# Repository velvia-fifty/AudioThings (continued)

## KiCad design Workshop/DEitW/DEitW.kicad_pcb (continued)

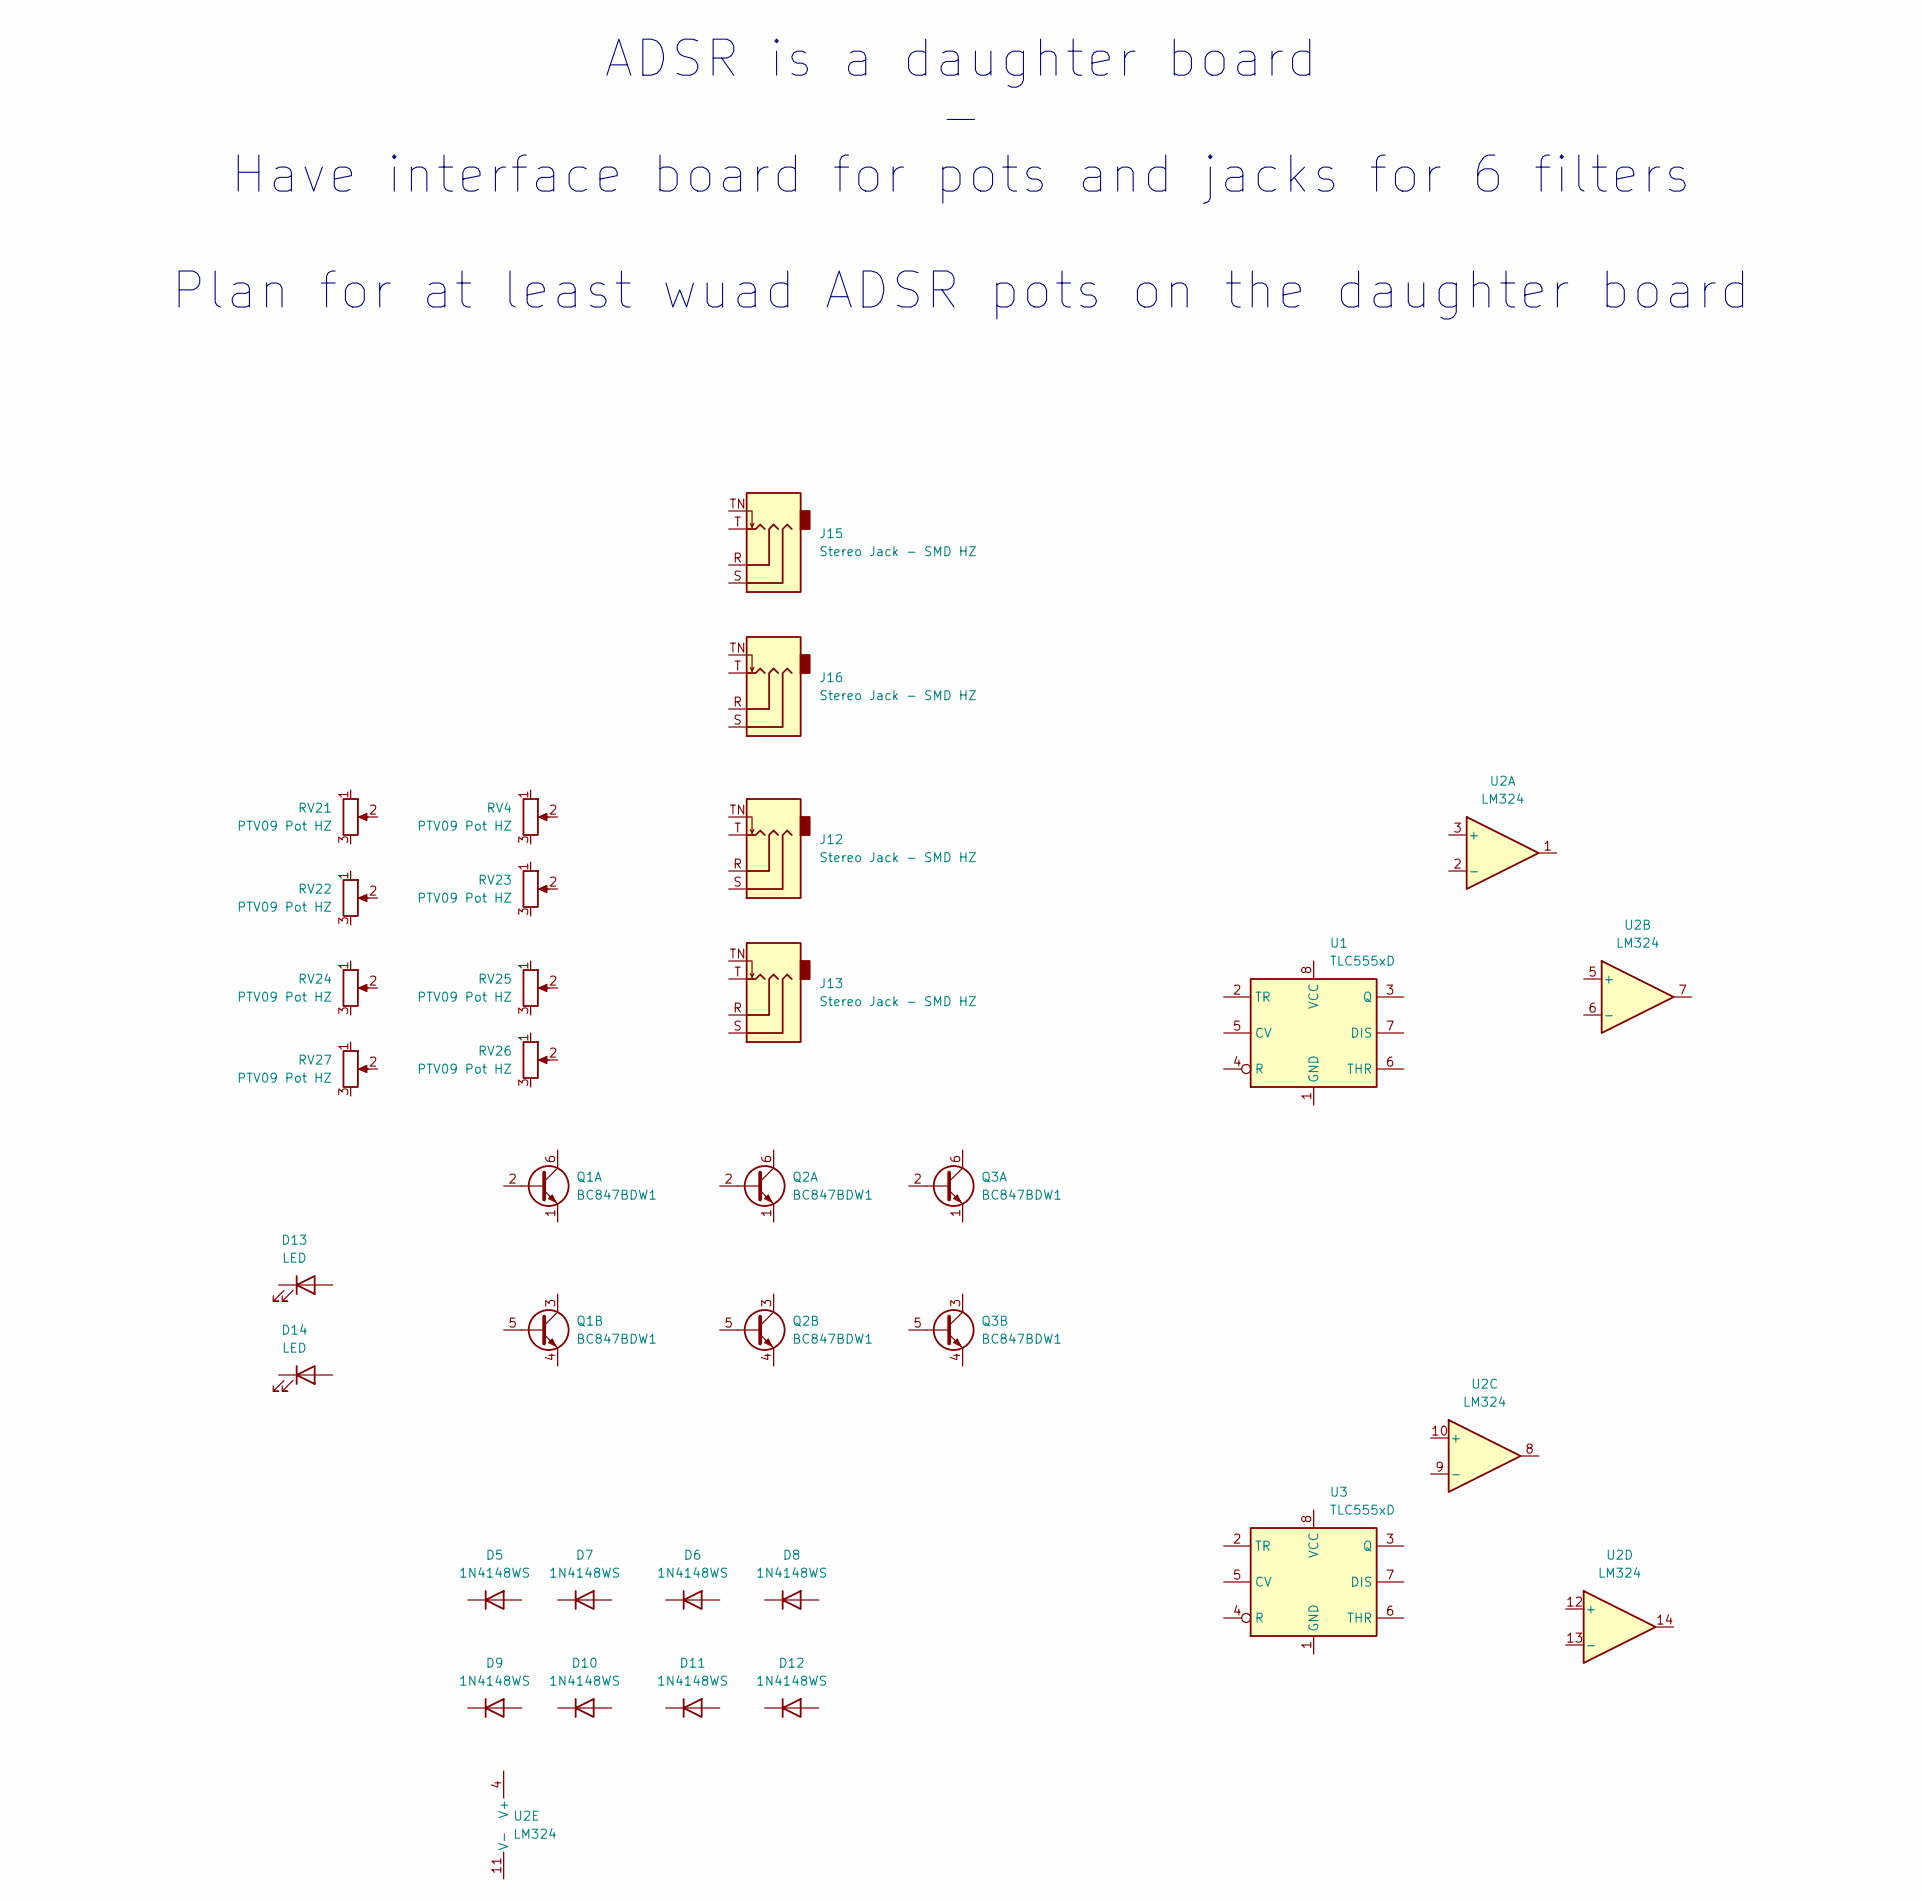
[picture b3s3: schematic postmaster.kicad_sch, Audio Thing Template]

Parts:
D5, D6, D7, D8, D9, D10, D11, D12: 1N4148WS; D_SOD-323
D13, D14: LED; LED_0805_2012Metric
J12, J13, J15, J16: Stereo Jack - SMD HZ; SMD_STEREO_CUI_SJ-3524-SMT_Horizontal
Q1, Q2, Q3: BC847BDW1; SOT-363_SC-70-6
RV4, RV21, RV22, RV23, RV24, RV25, RV26, RV27: PTV09 Pot HZ; Twelve_Turn_Trim_Bourns_3224J_Horizontal
U1, U3: TLC555xD; SOIC-8_3.9x4.9mm_P1.27mm
U2: LM324

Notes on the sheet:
ADSR is a daughter board - Have interface board for pots and jacks for 6 filters Plan for at least wuad ADSR pots on the daughter board

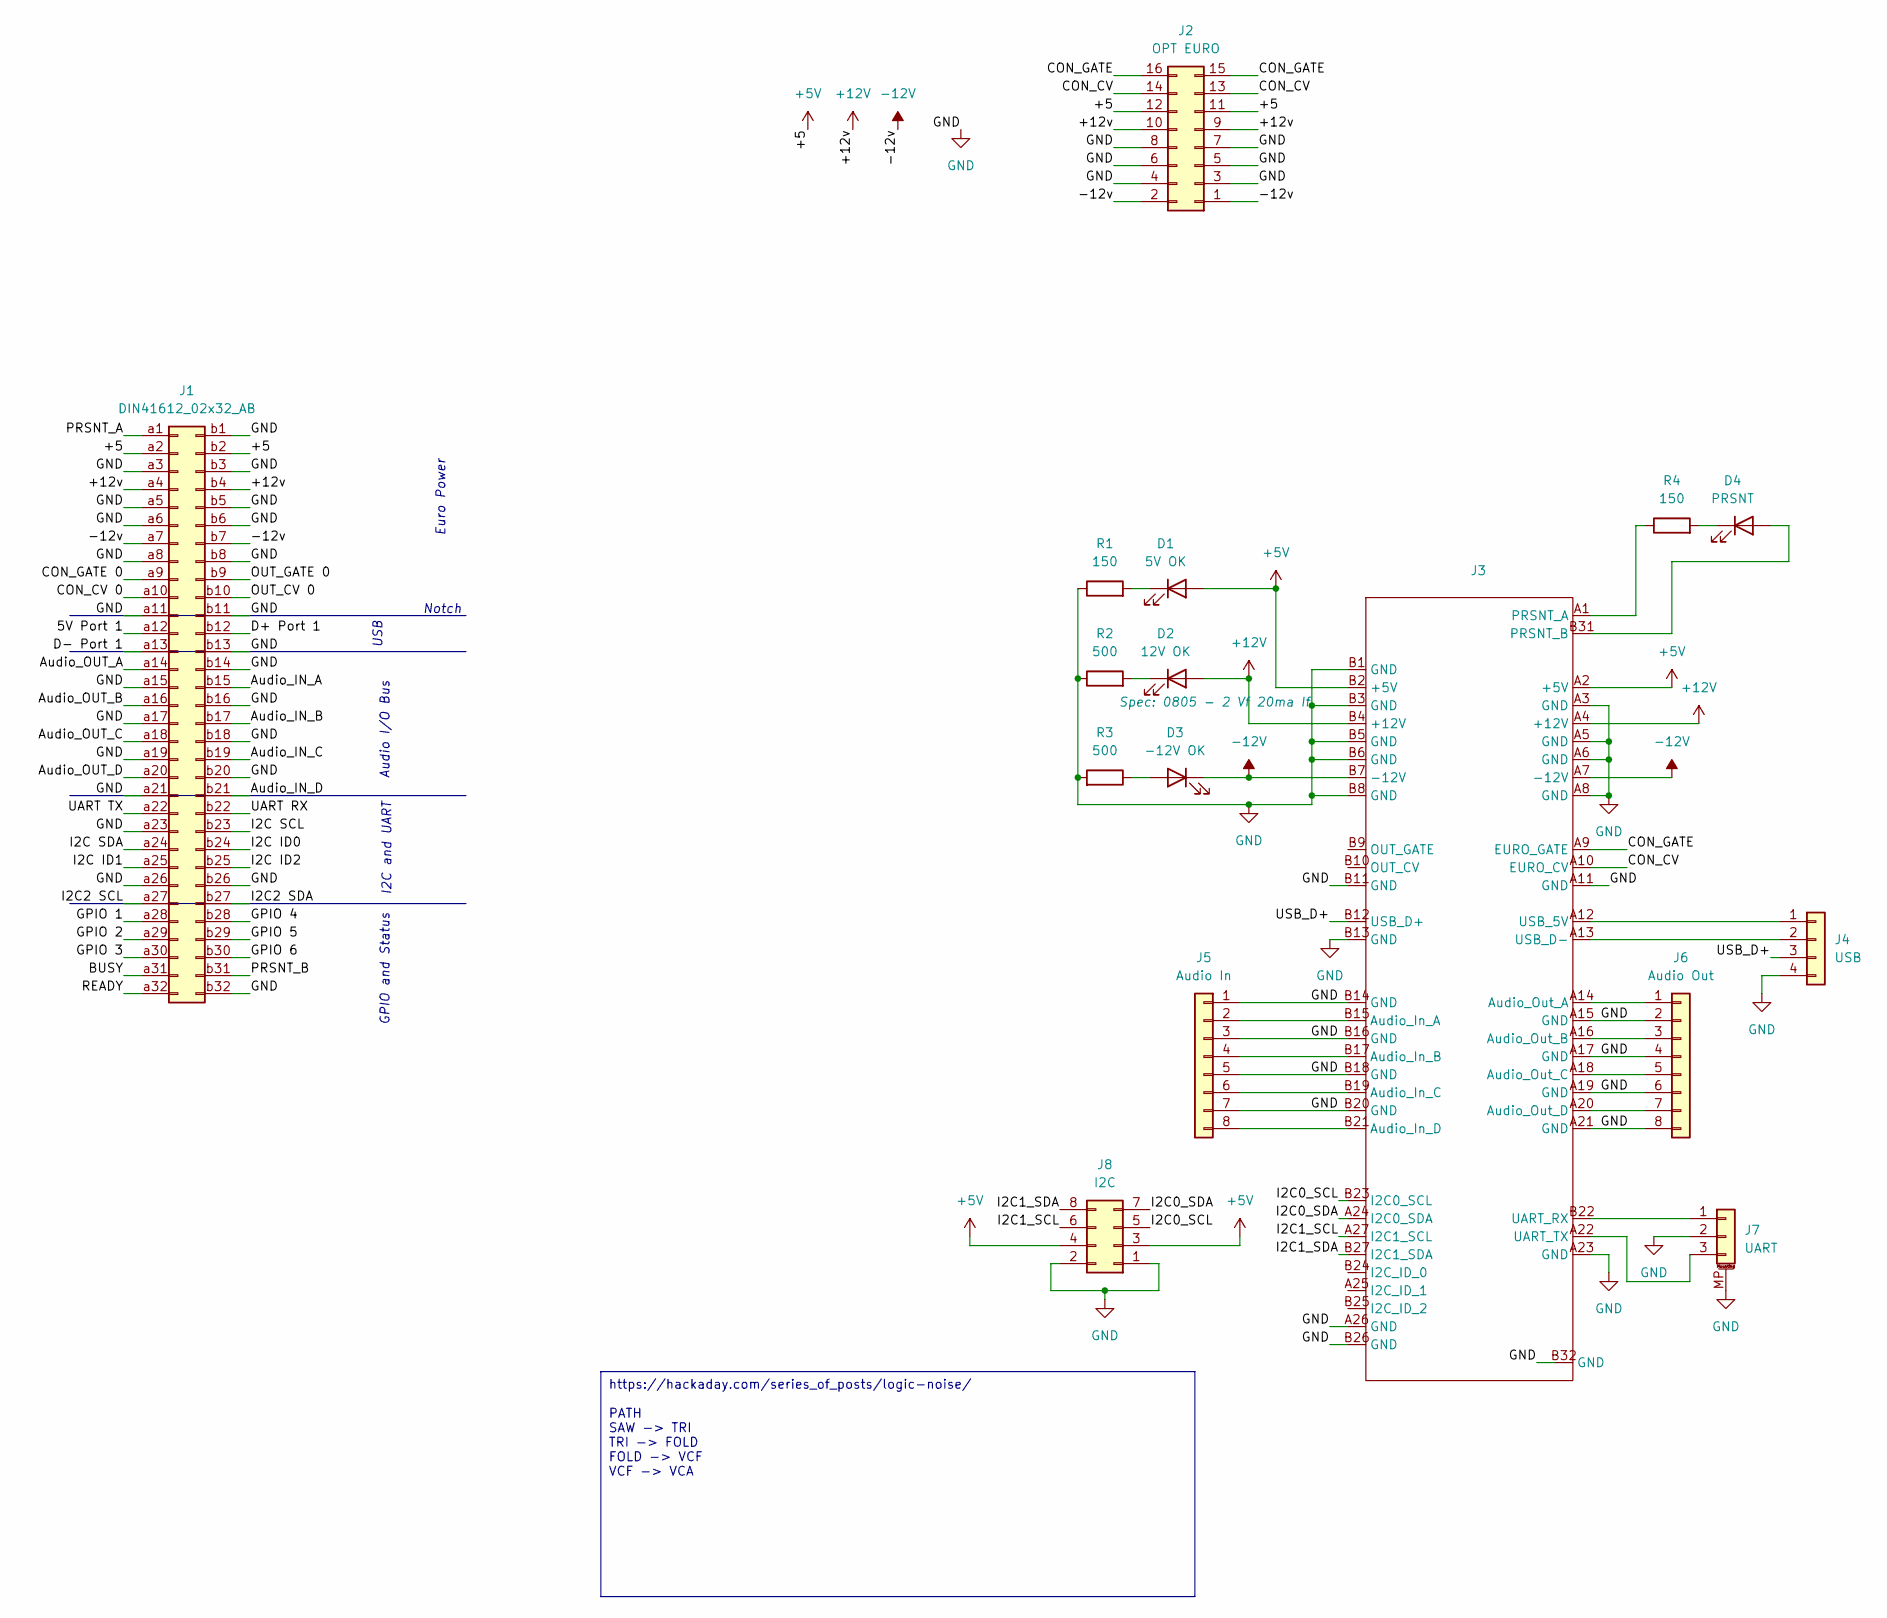
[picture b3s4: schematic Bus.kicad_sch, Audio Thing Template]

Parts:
D1: 5V OK; LED_0805_2012Metric_Pad1.15x1.40mm_HandSolder
D2: 12V OK; LED_0805_2012Metric_Pad1.15x1.40mm_HandSolder
D3: -12V OK; LED_0805_2012Metric_Pad1.15x1.40mm_HandSolder
D4: PRSNT; LED_0805_2012Metric_Pad1.15x1.40mm_HandSolder
J1: DIN41612_02x32_AB
J2: OPT EURO; EURORACK Right Angle
J3: BUS_PCIexpress_x4
J4: USB; PinHeader_1x04_P2.54mm_Vertical; Part Number 1-0401FBV0T
J5: Audio In; AMPHENOL_F33B-1A7Q1-E8C08
J6: Audio Out; AMPHENOL_F33B-1A7Q1-E8C08
J7: UART; CONN_BM03B-SRSS-TBLFSN_JST
J8: I2C; PinHeader_2x04_P2.54mm_Vertical
R1, R4: 150; R_0805_2012Metric_Pad1.20x1.40mm_HandSolder
R2, R3: 500; R_0805_2012Metric_Pad1.20x1.40mm_HandSolder

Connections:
+5V: D1.2 (A), J1.a2, J1.b2, J2.11, J2.12, J3.A2 (+5V), J3.B2 (+5V), J8.3, J8.4
+12V: D2.2 (A), J1.a4, J1.b4, J2.9, J2.10, J3.A4 (+12V), J3.B4 (+12V)
-12V: D3.1 (K), J1.a7, J1.b7, J2.1, J2.2, J3.A7 (-12V), J3.B7 (-12V)
/Bus/CON_CV: J2.13, J2.14, J3.A10 (EURO_CV)
/Bus/CON_GATE: J2.15, J2.16, J3.A9 (EURO_GATE)
/Bus/I2C0_SCL: J3.B23 (I2C0_SCL), J8.5
/Bus/I2C0_SDA: J3.A24 (I2C0_SDA), J8.7
/Bus/I2C1_SCL: J3.A27 (I2C1_SCL), J8.6
/Bus/I2C1_SDA: J3.B27 (I2C1_SDA), J8.8
/Bus/USB_D+: J3.B12 (USB_D+), J4.3
GND: J1.a3, J1.a5, J1.a6, J1.a8, J1.a11, J1.a15, J1.a17, J1.a19, J1.a21, J1.a23, J1.a26, J1.b1, J1.b3, J1.b5, J1.b6, J1.b8, J1.b11, J1.b13, J1.b14, J1.b16, J1.b18, J1.b20, J1.b26, J1.b32, J2.3, J2.4, J2.5, J2.6, J2.7, J2.8, J3.A3 (GND), J3.A5 (GND), J3.A6 (GND), J3.A8 (GND), J3.A11 (GND), J3.A15 (GND), J3.A17 (GND), J3.A19 (GND), J3.A21 (GND), J3.A23 (GND), J3.A26 (GND), J3.B1 (GND), J3.B3 (GND), J3.B5 (GND), J3.B6 (GND), J3.B8 (GND), J3.B11 (GND), J3.B13 (GND), J3.B14 (GND), J3.B16 (GND), J3.B18 (GND), J3.B20 (GND), J3.B26 (GND), J3.B32 (GND), J4.4, J5.1, J5.3, J5.5, J5.7, J6.2, J6.4, J6.6, J6.8, J7.2, J7.MP (MountPin), J8.1, J8.2, R1.1, R2.1, R3.2; also elsewhere on the board
unnamed: D1.1 (K), R1.2
unnamed: D2.1 (K), R2.2
unnamed: D3.2 (A), R3.1
unnamed: D4.2 (A), J3.B31 (PRSNT_B)
unnamed: D4.1 (K), R4.2
unnamed: J3.B15 (Audio_In_A), J5.2
unnamed: J3.B17 (Audio_In_B), J5.4
unnamed: J3.B19 (Audio_In_C), J5.6
unnamed: J3.B21 (Audio_In_D), J5.8
unnamed: J3.A14 (Audio_Out_A), J6.1
unnamed: J3.A16 (Audio_Out_B), J6.3
unnamed: J3.A18 (Audio_Out_C), J6.5
unnamed: J3.A20 (Audio_Out_D), J6.7
unnamed: J3.A1 (PRSNT_A), R4.1
unnamed: J3.B22 (UART_RX), J7.1
unnamed: J3.A22 (UART_TX), J7.3
unnamed: J3.A12 (USB_5V), J4.1
unnamed: J3.A13 (USB_D-), J4.2

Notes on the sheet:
https://hackaday.com/series_of_posts/logic-noise/ PATH SAW -> TRI TRI -> FOLD FOLD -> VCF VCF -> VCA
Audio I/O Bus
USB
Notch
Euro Power
GPIO and Status
I2C and UART

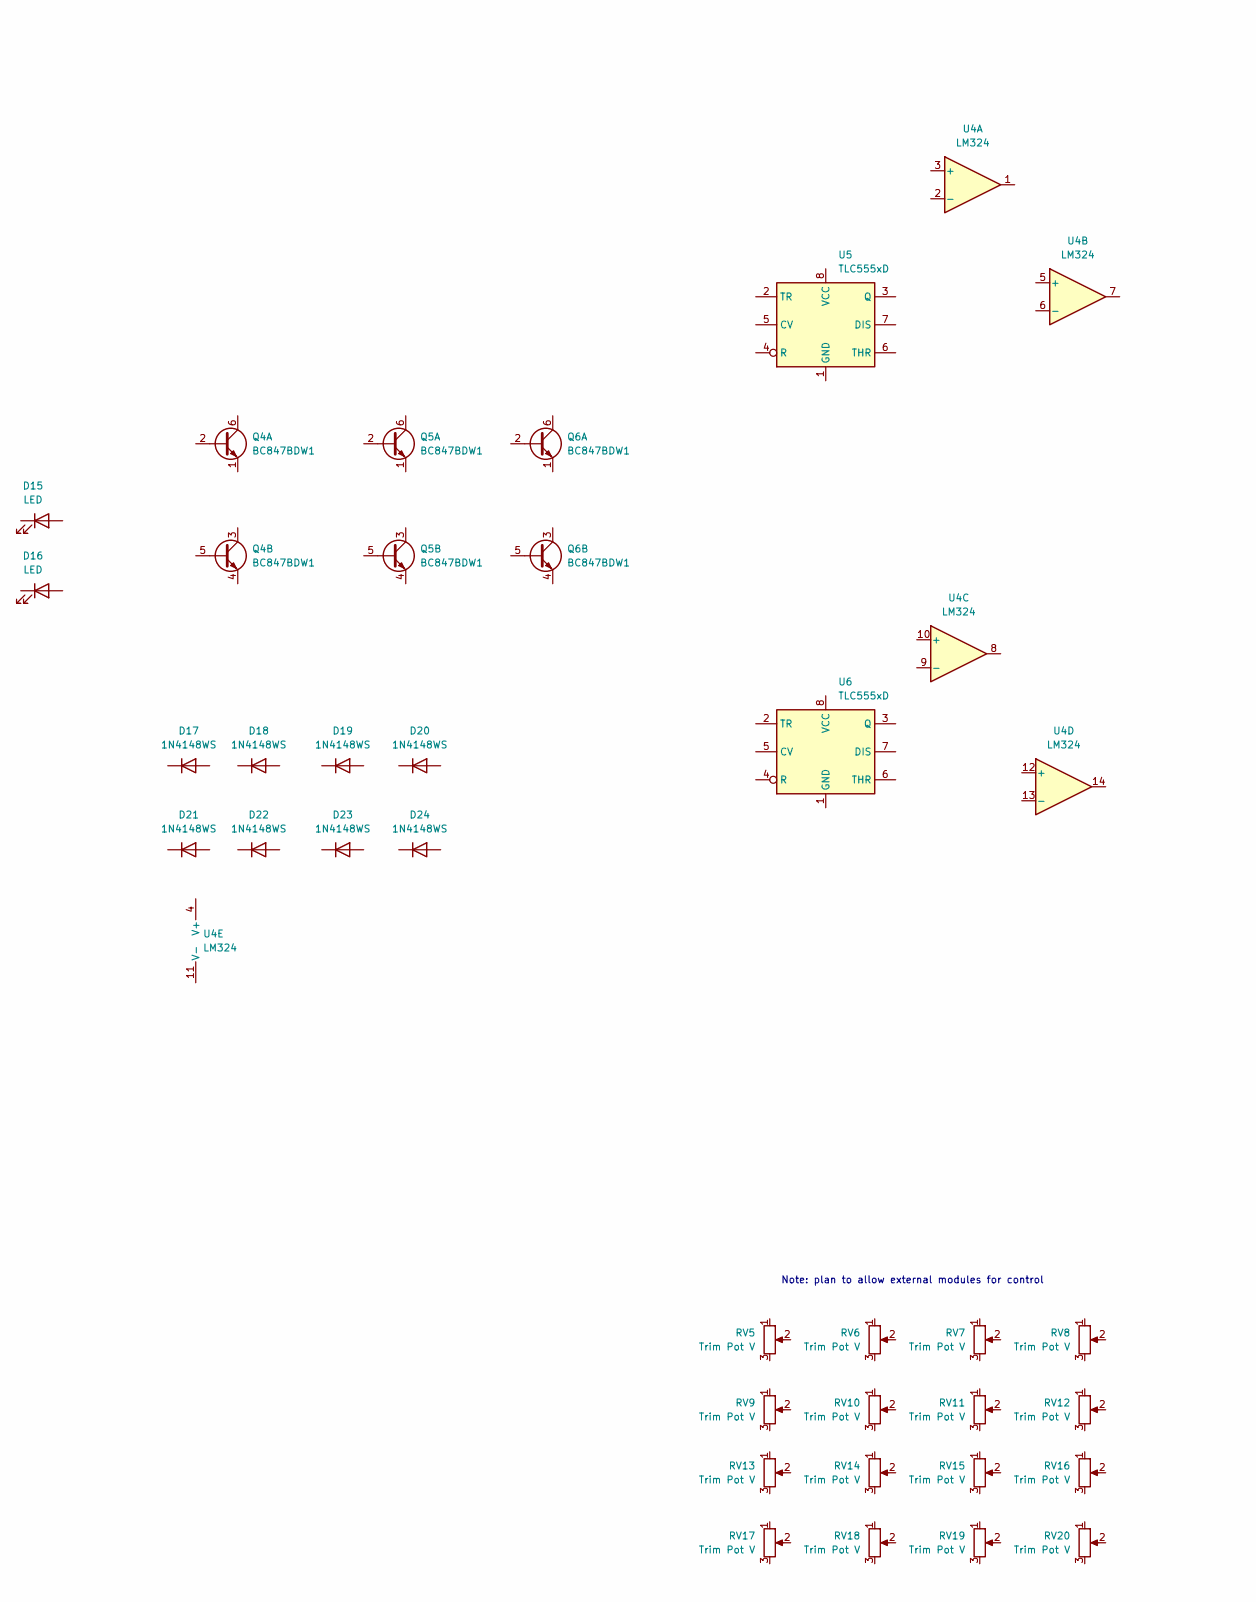
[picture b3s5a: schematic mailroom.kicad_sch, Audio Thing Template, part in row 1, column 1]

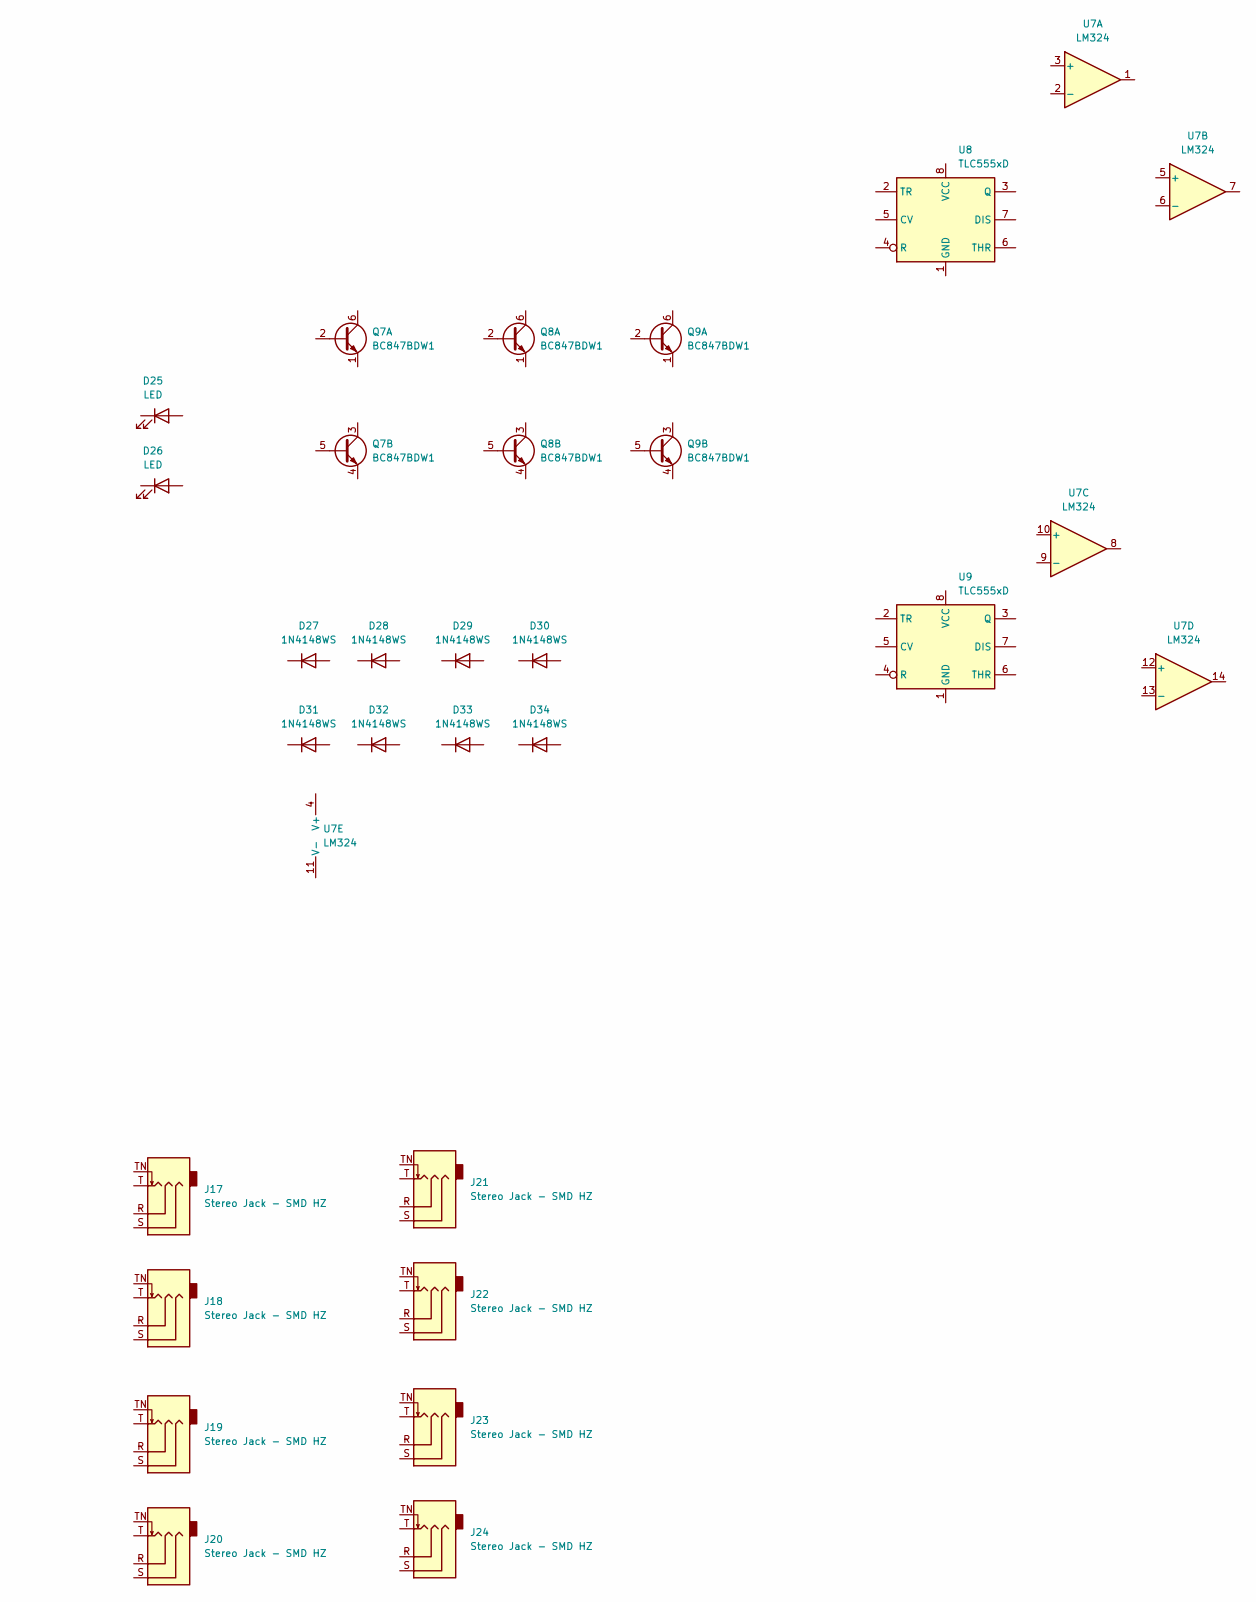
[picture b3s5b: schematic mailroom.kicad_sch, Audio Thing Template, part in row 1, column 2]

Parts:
D15, D16, D25, D26: LED; LED_0805_2012Metric
D17, D18, D19, D20, D21, D22, D23, D24, D27, D28, D29, D30, D31, D32, D33, D34: 1N4148WS; D_SOD-323
J17, J18, J19, J20, J21, J22, J23, J24: Stereo Jack - SMD HZ; SMD_STEREO_CUI_SJ-3524-SMT_Horizontal
Q4, Q5, Q6, Q7, Q8, Q9: BC847BDW1; SOT-363_SC-70-6
RV5, RV6, RV7, RV8, RV9, RV10, RV11, RV12, RV13, RV14, RV15, RV16, RV17, RV18, RV19, RV20: Trim Pot V; Twelve_Turn_Trim_Bourns_3224J_Horizontal
U4, U7: LM324
U5, U6, U8, U9: TLC555xD; SOIC-8_3.9x4.9mm_P1.27mm

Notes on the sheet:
Note: plan to allow external modules for control

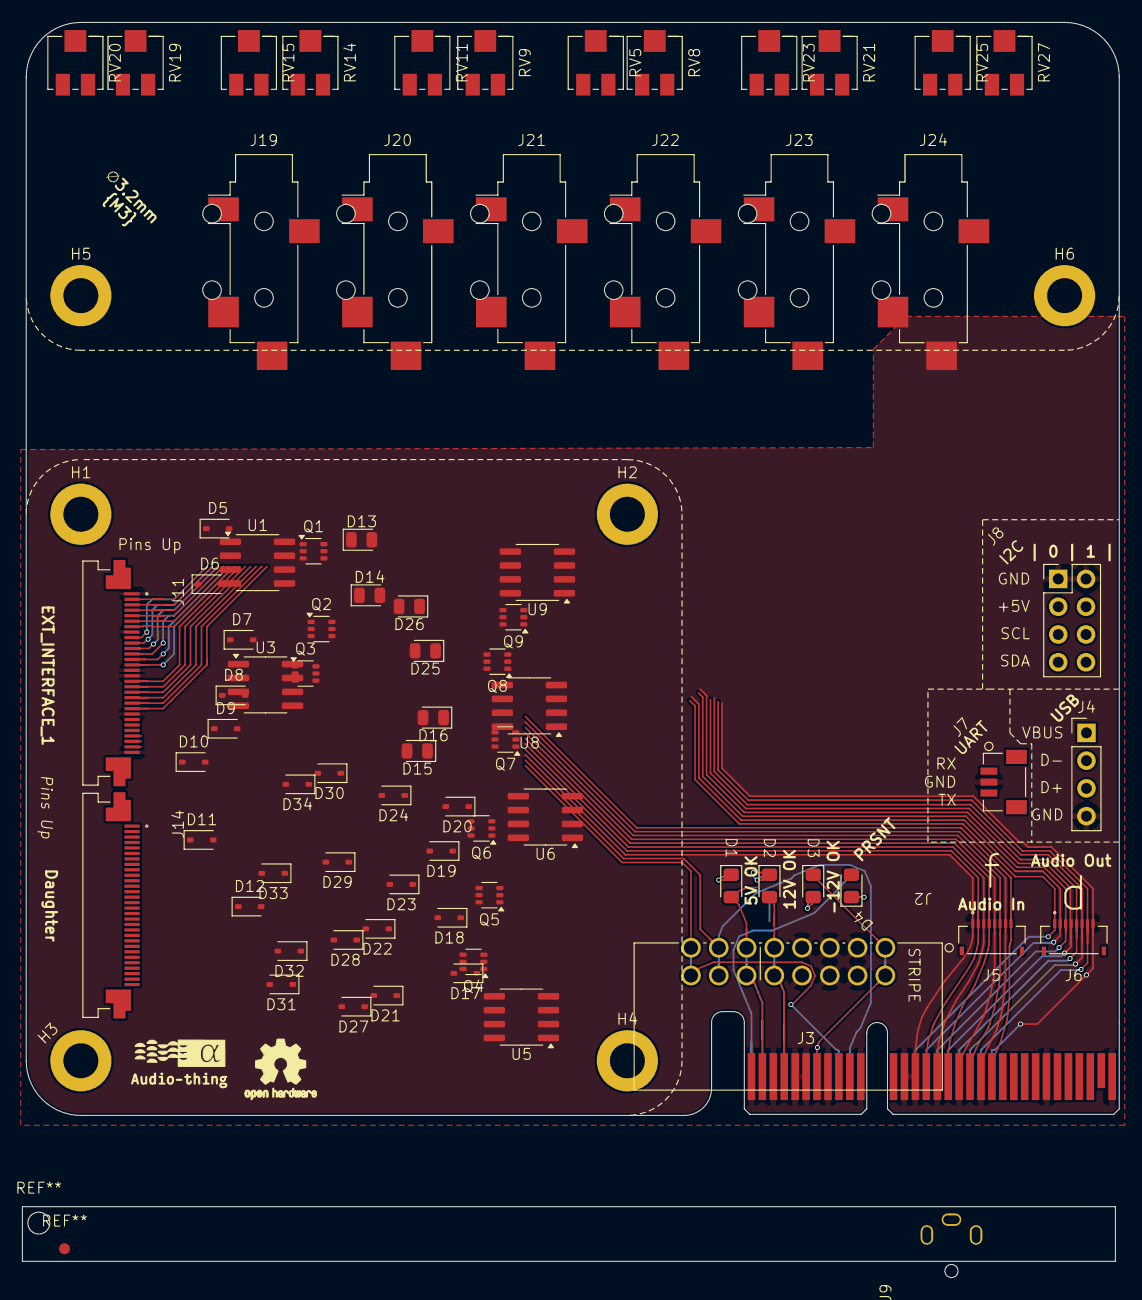
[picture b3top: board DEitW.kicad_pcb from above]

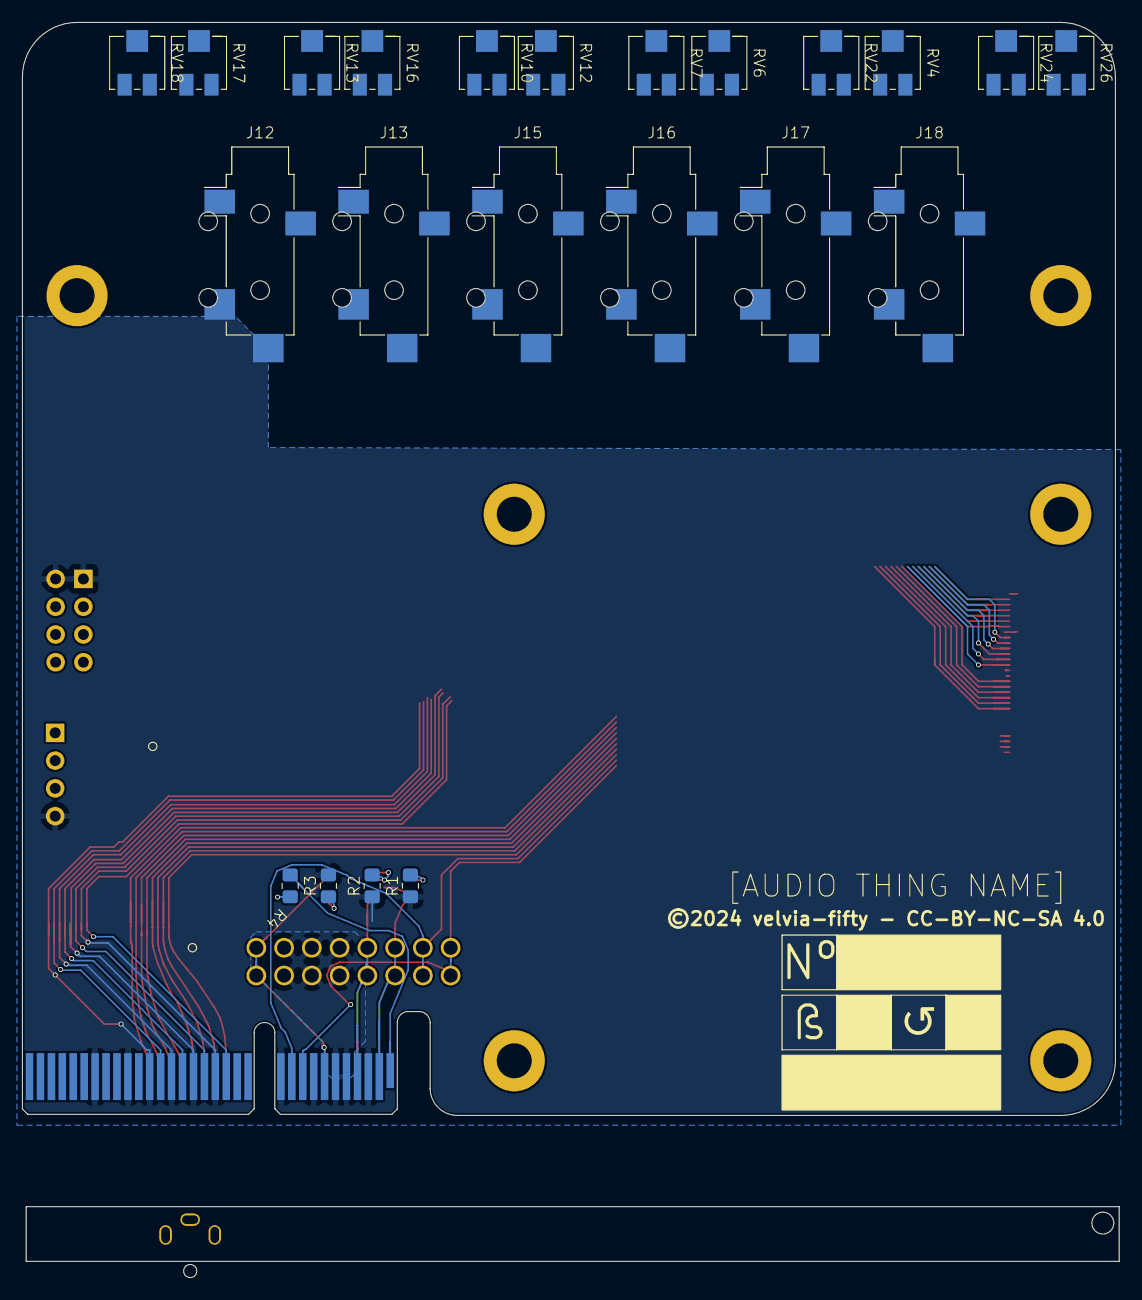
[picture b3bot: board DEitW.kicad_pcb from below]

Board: 2 copper layers, 100.0 x 100.0 mm, 105 parts (22 on the bottom side), 29 nets.

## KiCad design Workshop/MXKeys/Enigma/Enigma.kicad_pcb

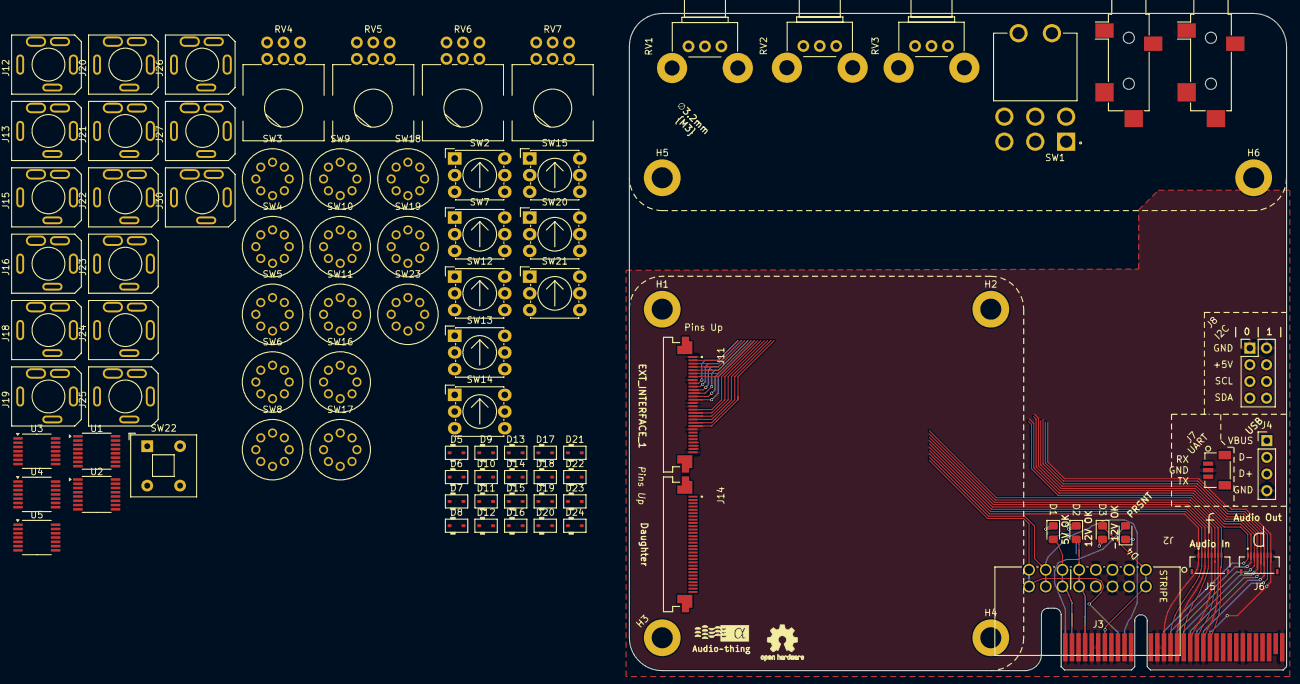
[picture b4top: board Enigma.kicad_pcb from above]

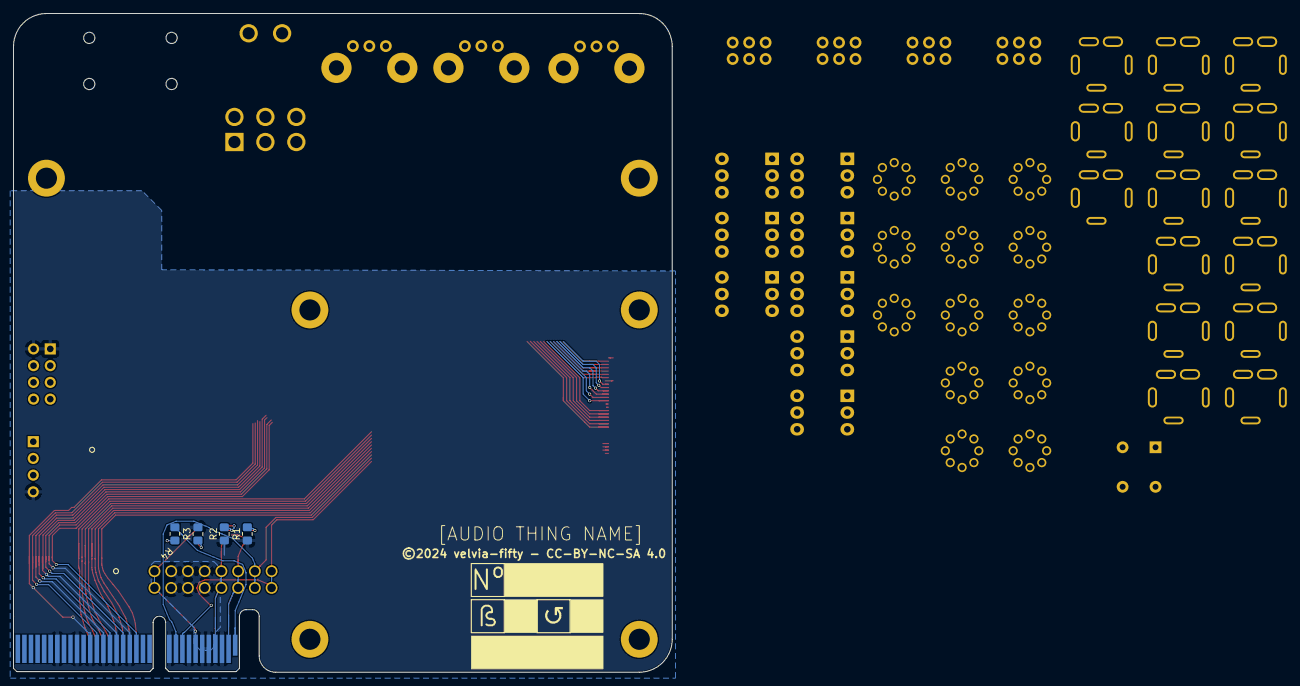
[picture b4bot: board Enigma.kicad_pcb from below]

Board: 2 copper layers, 100.0 x 100.0 mm, 95 parts (4 on the bottom side), 79 nets.

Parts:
D1: 5V OK; LED_0805_2012Metric_Pad1.15x1.40mm_HandSolder
D2: 12V OK; LED_0805_2012Metric_Pad1.15x1.40mm_HandSolder
D3: -12V OK; LED_0805_2012Metric_Pad1.15x1.40mm_HandSolder
D4: PRSNT; LED_0805_2012Metric_Pad1.15x1.40mm_HandSolder
D5, D6, D7, D8, D9, D10, D11, D12, D13, D14, D15, D16, D17, D18, D19, D20, D21, D22, D23, D24: 1N4148WS; D_SOD-323
H1, H2, H3, H4, H5, H6: M3; MountingHole_3.2mm_M3_DIN965_Pad
J2: OPT EURO; EURORACK Right Angle
J3: BUS_PCIexpress_x4
J4: USB; PinHeader_1x04_P2.54mm_Vertical
J5: Audio In; AMPHENOL_F33B-1A7Q1-E8C08
J6: Audio Out; AMPHENOL_F33B-1A7Q1-E8C08
J7: UART; CONN_BM03B-SRSS-TBLFSN_JST
J8: I2C; PinHeader_2x04_P2.54mm_Vertical
J9, J10: Stereo Jack - SMD HZ; SMD_STEREO_CUI_SJ-3524-SMT_Horizontal
J11: EXT_INTERFACE_1; AMPHENOL_SFV30R-4STE1HLF - FFC - 30 RA
J12: Input 1; SJ3-3505
J13: Input 2; SJ3-3505
J14: Daughter; AMPHENOL_SFV30R-4STE1HLF - FFC - 30 RA
J15: Input 3; SJ3-3505
J16: Input 4; SJ3-3505
J18: Filter EXT 2; SJ3-3505
J19: Filter EXT 3; SJ3-3505
J20: Filter EXT 4; SJ3-3505
J21: Output Bypass 1; SJ3-3505
J22: Mix Out Channel 1; SJ3-3505
J23: Mix Out Channel 2; SJ3-3505
J24: Mix Out Channel 3; SJ3-3505
J25: Mix Out Channel 4; SJ3-3505
J26: Bypass Return/Filter Out 1; SJ3-3505
J27: Mix^{2}; SJ3-3505
J30: Bypass Send/Filter In 1; SJ3-3505
R1, R4: 150; R_0805_2012Metric_Pad1.20x1.40mm_HandSolder
R2, R3: 500; R_0805_2012Metric_Pad1.20x1.40mm_HandSolder
RV1, RV2, RV3: PTV09 Pot HZ; Potentiometer_Bourns_PTV09A-2_Single_Horizontal
RV4, RV5, RV6, RV7: 10k B; 2hp_Alps_RK09L_Double_Vertical
SW1: Micro Toggle; DPDT Micro SW_1825138-7
SW2: Input Route 1; Nidec_Copal_SH-7010C
SW3: Input Handoff R 1; RM-SWITCH
SW4: Input Handoff R 2; RM-SWITCH
SW5: Input Handoff L 2; RM-SWITCH
SW6: Input Handoff L 1; RM-SWITCH
SW7: Input Route 2; Nidec_Copal_SH-7010C
SW8: Input Handoff R 3; RM-SWITCH
SW9: Input Handoff R 4; RM-SWITCH
SW10: Input Handoff L 3; RM-SWITCH
SW11: Input Handoff L 4; RM-SWITCH
SW12: Input Route 3; Nidec_Copal_SH-7010C
SW13: Input Route 4; Nidec_Copal_SH-7010C
SW14: FIlter Route 1; Nidec_Copal_SH-7010C
SW15: Output Mix 1; Nidec_Copal_SH-7010C
SW16: Stereo Mix R 1; RM-SWITCH
SW17: Stereo Mix R 2; RM-SWITCH
SW18: Stereo Mix R 3; RM-SWITCH
SW19: Stereo Mix R 4; RM-SWITCH
SW20: FIlter Route Bypass; Nidec_Copal_SH-7010C
SW21: Amplifier Route Bypass; Nidec_Copal_SH-7010C
SW22: Bypass?; SW_Push_2P1T_Toggle_CK_PVA1xxH1xxxxxxV2
SW23: Control Config; RM-SWITCH
U1, U2: DG403DVZ; TSSOP-16_4.4x5mm_P0.65mm
U3: 40106; TSSOP-14_4.4x5mm_P0.65mm
U4, U5: CD4066BPW; TSSOP-14_4.4x5mm_P0.65mm

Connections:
5v: SW22.1, SW22.3, U1.12 (VL), U2.12 (VL)
+5V: D1.2 (A), J2.11, J2.12, J3.A2 (+5V), J3.B2 (+5V), J8.3, J8.4
+12v: D2.2 (A), J2.9, J2.10, J3.A4 (+12V), J3.B4 (+12V), U1.11 (V+), U2.11 (V+)
-12v: D3.1 (K), J2.1, J2.2, J3.A7 (-12V), J3.B7 (-12V), U1.14 (V-), U2.14 (V-)
/Assert All Inputs: J12.T, J13.T, J15.T, J16.T, SW2.C, SW3.5, SW3.6, SW3.7, SW4.5, SW4.6, SW4.7, SW5.5, SW5.6, SW5.7, SW5.8, SW6.5, SW6.6, SW6.7, SW6.8, SW7.C, SW8.5, SW8.6, SW8.7, SW9.5, SW9.6, SW9.7, SW10.5, SW10.6, SW10.7, SW10.8, SW11.5, SW11.6, SW11.7, SW11.8, SW12.C, SW13.C, SW16.5, SW17.5, SW18.5, SW19.5, U4.1, U4.4, U4.8, U4.11
/Bus/CON_CV: J2.13, J2.14, J3.A10 (EURO_CV)
/Bus/CON_GATE: J2.15, J2.16, J3.A9 (EURO_GATE)
/Bus/I2C0_SCL: J3.B23 (I2C0_SCL), J8.5
/Bus/I2C0_SDA: J3.A24 (I2C0_SDA), J8.7
/Bus/I2C1_SCL: J3.A27 (I2C1_SCL), J8.6
/Bus/I2C1_SDA: J3.B27 (I2C1_SDA), J8.8
/Bus/USB_D+: J3.B12 (USB_D+), J4.3
/IN 1 TN: J12.TN, SW4.3, SW5.3, SW8.4, SW9.2, SW10.4, SW11.2
/IN 2 TN: J13.TN, SW3.2, SW6.2, SW8.3, SW9.4, SW10.3, SW11.4
/IN 3 TN: J15.TN, SW3.4, SW4.2, SW5.2, SW6.4, SW9.3, SW11.3
/IN 4 TN: J16.TN, SW3.3, SW4.4, SW5.4, SW6.3, SW8.2, SW10.2
Amplifier 1: D21.2 (A), SW14.1, SW16.7, SW20.1
Amplifier 2: D22.2 (A), SW14.2, SW17.7, SW20.2
Amplifier 3: D23.2 (A), SW14.4, SW18.7, SW20.4
Amplifier 4: D24.2 (A), SW14.8, SW19.7, SW20.8
COM: U1.13 (GND), U2.13 (GND)
Channel 1: J22.T, RV4.3, SW15.1, SW16.2, SW17.4, SW19.3, SW21.1
Channel 2: J23.T, RV5.3, SW15.2, SW16.3, SW17.2, SW18.4, SW21.2
Channel 3: J24.T, RV6.3, SW15.4, SW17.3, SW18.2, SW19.4, SW21.4
Channel 4: J25.T, RV7.3, SW15.8, SW16.4, SW18.3, SW19.2, SW21.8
Filter 1: D5.2 (A), D9.2 (A), D13.2 (A), D17.2 (A), SW2.1, SW7.1, SW12.1, SW13.1, SW16.6, U1.4 (S3), U1.5 (S4), U1.16 (S1)
Filter 2: D6.2 (A), D10.2 (A), D14.2 (A), D18.2 (A), J18.TN, SW2.2, SW7.2, SW12.2, SW13.2, SW17.6
Filter 3: D7.2 (A), D11.2 (A), D15.2 (A), D19.2 (A), J19.TN, SW2.4, SW7.4, SW12.4, SW13.4, SW18.6
Filter 4: D8.2 (A), D12.2 (A), D16.2 (A), D20.2 (A), J20.TN, SW2.8, SW7.8, SW12.8, SW13.8, SW19.6
GND: J2.3, J2.4, J2.5, J2.6, J2.7, J2.8, J3.A3 (GND), J3.A5 (GND), J3.A6 (GND), J3.A8 (GND), J3.A11 (GND), J3.A15 (GND), J3.A17 (GND), J3.A19 (GND), J3.A21 (GND), J3.A23 (GND), J3.A26 (GND), J3.B1 (GND), J3.B3 (GND), J3.B5 (GND), J3.B6 (GND), J3.B8 (GND), J3.B11 (GND), J3.B13 (GND), J3.B14 (GND), J3.B16 (GND), J3.B18 (GND), J3.B20 (GND), J3.B26 (GND), J3.B32 (GND), J4.4, J5.1, J5.3, J5.5, J5.7, J6.2, J6.4, J6.6, J6.8, J7.2, J8.1, J8.2, J11.1, J11.8, J11.15, J11.16, J11.23, J11.30, J12.S, J13.S, J15.S, J16.S, J18.S, J19.S, J20.S, J21.S, J22.S, J23.S, J24.S, J25.S, J26.S, J27.S, J30.S, R1.1, R2.1, R3.2, RV4.1, RV4.4, RV5.1, RV5.4, RV6.1, RV6.4, RV7.1, RV7.4
LPF OUTPUT: U2.5 (S4), U2.16 (S1)
unnamed: D1.1 (K), R1.2
unnamed: D2.1 (K), R2.2
unnamed: D3.2 (A), R3.1
unnamed: D4.2 (A), J3.B31 (PRSNT_B)
unnamed: D4.1 (K), R4.2
unnamed: D5.1 (K), D6.1 (K), D7.1 (K), D8.1 (K), U3.1
unnamed: D9.1 (K), D10.1 (K), D11.1 (K), D12.1 (K), U3.3
unnamed: D13.1 (K), D14.1 (K), D15.1 (K), D16.1 (K), U3.5
unnamed: D17.1 (K), D18.1 (K), D19.1 (K), D20.1 (K), U3.9
unnamed: D21.1 (K), D22.1 (K), D23.1 (K), D24.1 (K), U3.11
unnamed: J3.B15 (Audio_In_A), J5.2
unnamed: J3.B17 (Audio_In_B), J5.4
unnamed: J3.B19 (Audio_In_C), J5.6
unnamed: J3.B21 (Audio_In_D), J5.8
unnamed: J3.A14 (Audio_Out_A), J6.1
unnamed: J3.A16 (Audio_Out_B), J6.3
unnamed: J3.A18 (Audio_Out_C), J6.5
unnamed: J3.A20 (Audio_Out_D), J6.7
unnamed: J3.A1 (PRSNT_A), R4.1
unnamed: J3.B22 (UART_RX), J7.1
unnamed: J3.A22 (UART_TX), J7.3
unnamed: J3.A12 (USB_5V), J4.1
unnamed: J3.A13 (USB_D-), J4.2
unnamed: J12.R, SW3.8
unnamed: J13.R, SW4.8
unnamed: J15.R, SW8.8
unnamed: J16.R, SW9.8
unnamed: J21.TN, SW15.C
unnamed: J27.R, RV4.5, RV5.5, RV6.5, RV7.5
unnamed: J27.T, RV4.2, RV5.2, RV6.2, RV7.2
unnamed: SW20.C, U4.2, U4.3, U4.9, U4.10, U5.1
unnamed: SW21.C, U5.2
unnamed: J30.T, U1.1 (D1), U1.3 (D3)
unnamed: J30.TN, U1.6 (D4), U1.8 (D2)
unnamed: SW22.2, U1.10 (IN2), U1.15 (IN1)
unnamed: J26.T, U2.1 (D1), U2.3 (D3)
unnamed: J26.TN, U2.6 (D4), U2.8 (D2)
unnamed: SW22.4, U2.10 (IN2), U2.15 (IN1)
unnamed: SW14.C, U2.4 (S3)
unnamed: U3.2, U4.13
unnamed: U3.4, U4.5
unnamed: U3.6, U4.6
unnamed: U3.8, U4.12
unnamed: U3.10, U5.13
Stereo Channel 1: J22.R, RV4.6, SW16.8
Stereo Channel 2: J23.R, RV5.6, SW17.8
Stereo Channel 3: J24.R, RV6.6, SW18.8
Stereo Channel 4: J25.R, RV7.6, SW19.8
